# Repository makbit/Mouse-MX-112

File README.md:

# Mouse MX-112 - Free computer mouse with USB and PS/2 interfaces

This is a computer mouse with USB and PS/2 intefaces. There are 3 buttons and a wheel. The PCB is designed to be placed in a cheap plastic case manufactured in china. I have used the plastic case and lenses from the RX-112 mouse as a donor.

The mouse is compatible with Windows and Linux OS.

The device is based on a Silabs 8-bit MCU [EFM8UB20F32](https://www.silabs.com/mcu/8-bit/efm8-universal-bee/device.efm8ub20f32g-qfp32). This MCU has a Fullspeed USB controller and adjustable internal oscillator.

### Advantages of this mouse:
* Open hardware and software design;
* Compliant to hardware and software specification;
* Popular optical sensor ADNS-5050 with 1000+cpi and 8g;
* All electronic components are available in your local shop;
* I use it myself.

The [`Hardware`](Hardware) folder contains Eagle CAD 9 schematics files. The board schematics can be found in the[`Hardware/Mouse-112-sh.png`](Hardware/Mouse-112-sh.png) file.

The firmware is under development...

##### Some pictures of this Mouse MX-112:cool:

### Project Info

### TODO :pen:
 - [X] Solder;
 - [X] Test hardware;
 - [ ] Write firmware;
 - [ ] Test firmware;
 - [ ] Find a sponsor :smile:

[GitHub readme tips&tricks](https://help.github.com/articles/basic-writing-and-formatting-syntax/)

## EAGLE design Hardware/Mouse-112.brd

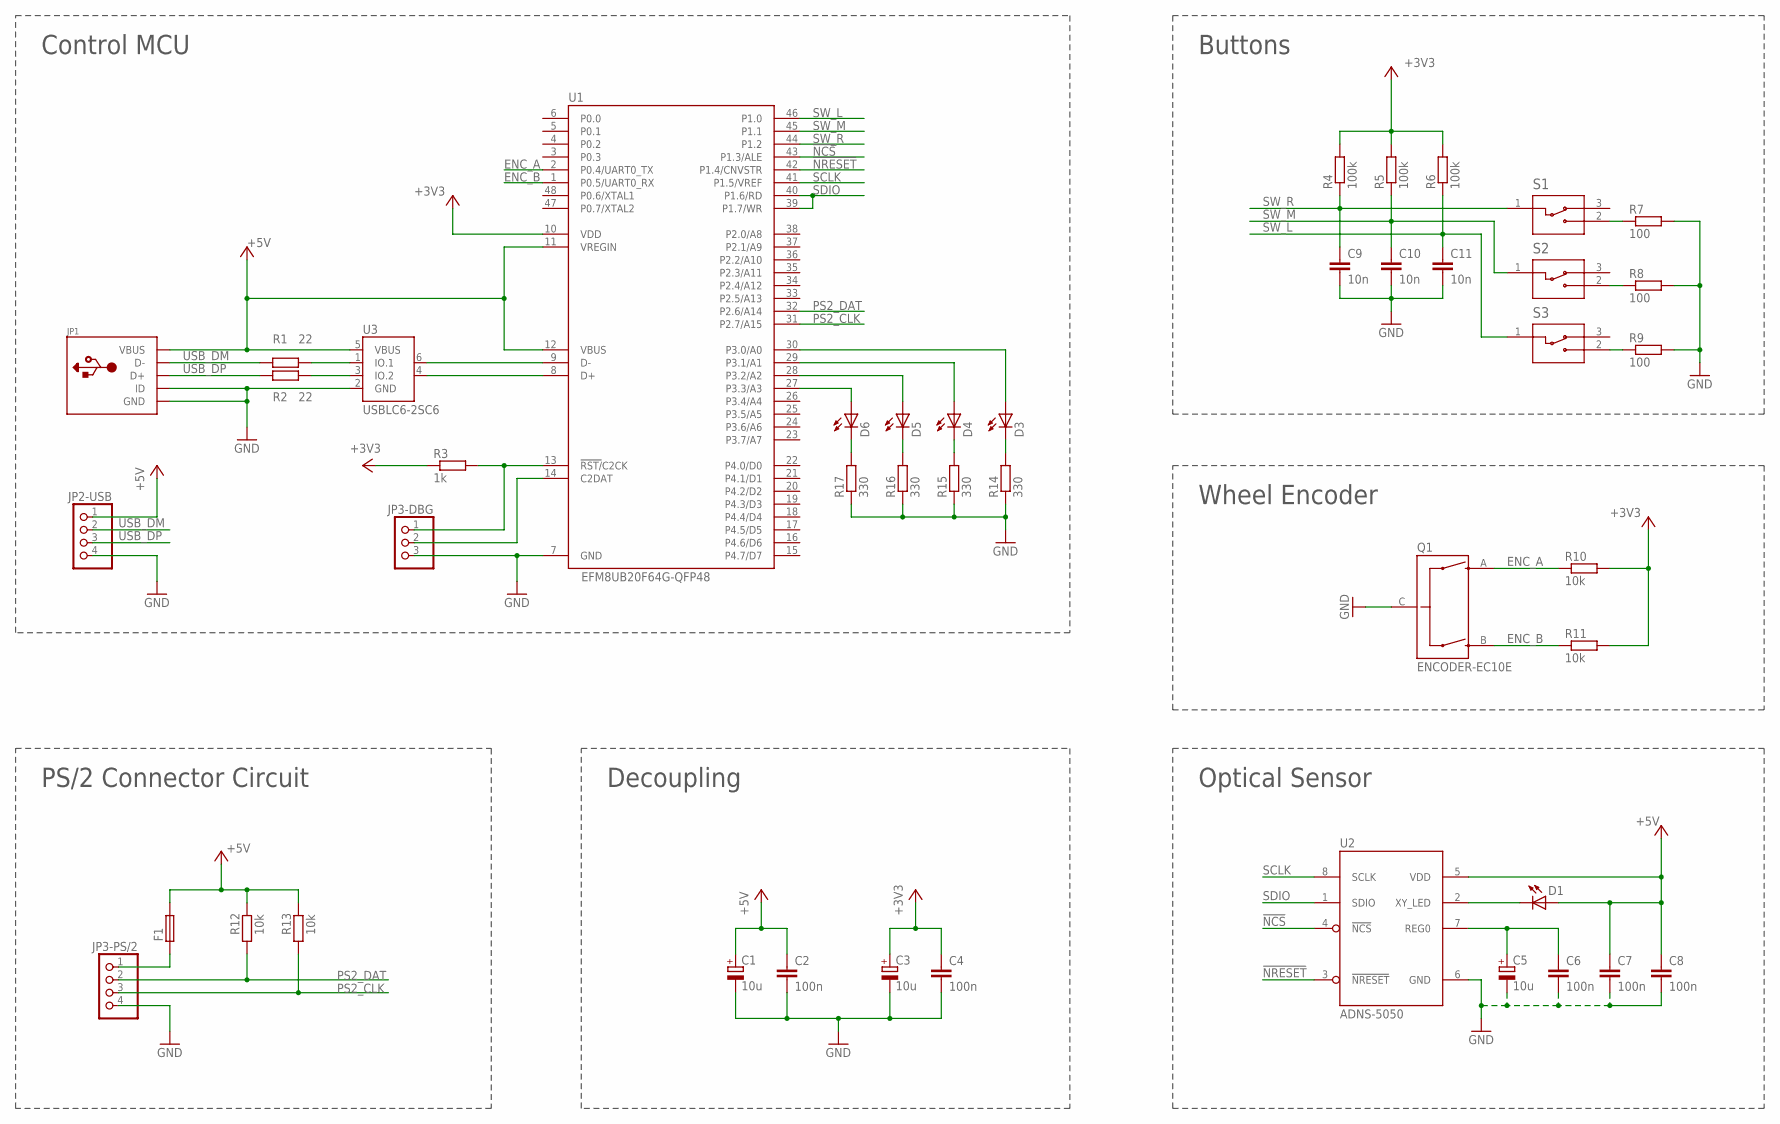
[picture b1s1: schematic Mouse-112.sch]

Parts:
C1, C3, C5: 10u; RCL-1206F-POL
C2, C4, C6, C7, C8: 100n; RCL-0805F
C9, C10, C11: 10n; RCL-0805F
D1: LED5MM
D3, D4, D5, D6: LEDLED-0805F; LED-0805F
F1: FUSE-NSMF; RCL-1206F
JP1: USB-MINI; USB-MINIB
JP2-USB, JP3-PS/2: PINHD-1X4; 1X04
JP3-DBG: PINHD-1X3; 1X03
Q1: ENCODER-EC10E; ENCODER-10MM
R1, R2: 22; RCL-0805F
R3: 1k; RCL-0805F
R4, R5, R6: 100k; RCL-0805F
R7, R8, R9: 100; RCL-0805F
R10, R11, R12, R13: 10k; RCL-0805F
R14, R15, R16, R17: 330; RCL-0805F
S1, S2, S3: SWITCH-D2F-01; SWITCH-D2F-01L-12.8X5.8MM
U1: EFM8UB20F64G-QFP48; QFP48-7X7-0P5MM
U2: ADNS-5050; ADNS-5050-DIP-8
U3: USBLC6-2SC6; SOT-23-6L

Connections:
!NCS: U1.43 (P1.3/ALE), U2.4 (!NCS)
!NRESET: U1.42 (P1.4/CNVSTR), U2.3 (!NRESET)
+3V3: C3.+, C4.1, R3.1, R4.2, R5.2, R6.2, R10.2, R11.2, U1.10 (VDD)
+5V: C1.+, C2.1, C7.1, C8.1, D1.A, F1.2, JP1.VBUS, JP2-USB.1, R12.2, R13.2, U1.11 (VREGIN), U1.12 (VBUS), U2.5 (VDD), U3.5 (VBUS)
C2CK: JP3-DBG.1, R3.2, U1.13 (!RST/!C2CK)
C2DAT: JP3-DBG.2, U1.14 (C2DAT)
ENC_A: Q1.A, R10.1, U1.2 (P0.4/UART0_TX)
ENC_B: Q1.B, R11.1, U1.1 (P0.5/UART0_RX)
GND: C1.-, C2.2, C3.-, C4.2, C5.-, C6.2, C7.2, C8.2, C9.2, C10.2, C11.2, JP1.GND, JP1.ID, JP2-USB.4, JP3-DBG.3, JP3-PS/2.4, Q1.C, R7.2, R8.2, R9.2, R14.1, R15.1, R16.1, R17.1, U1.7 (GND), U2.6 (GND), U3.2 (GND)
unnamed: D1.K (C), U2.2 (XY_LED)
unnamed: D4.A, U1.29 (P3.1/A1)
unnamed: R2.2, U3.3 (IO.2)
unnamed: R1.2, U3.1 (IO.1)
unnamed: D3.A, U1.30 (P3.0/A0)
unnamed: D4.C, R15.2
unnamed: U1.9 (D-), U3.6 (IO_1)
unnamed: U1.8 (D+), U3.4 (IO_2)
unnamed: D3.C, R14.2
unnamed: F1.1, JP3-PS/2.1
unnamed: D5.C, R16.2
unnamed: R7.1, S1.2
unnamed: R8.1, S2.2
unnamed: R9.1, S3.2
unnamed: D5.A, U1.28 (P3.2/A2)
unnamed: D6.A, U1.27 (P3.3/A3)
unnamed: D6.C, R17.2
PS2_CLK: JP3-PS/2.3, R13.1, U1.31 (P2.7/A15)
PS2_DAT: JP3-PS/2.2, R12.1, U1.32 (P2.6/A14)
REG0: C5.+, C6.1, U2.7 (REG0)
SCLK: U1.41 (P1.5/VREF), U2.8 (SCLK)
SDIO: U1.39 (P1.7/WR), U1.40 (P1.6/RD), U2.1 (SDIO)
SW_L: C11.1, R6.1, S3.1, U1.46 (P1.0)
SW_M: C10.1, R5.1, S2.1, U1.45 (P1.1)
SW_R: C9.1, R4.1, S1.1, U1.44 (P1.2)
USB_DM: JP1.D-, JP2-USB.2, R1.1
USB_DP: JP1.D+, JP2-USB.3, R2.1

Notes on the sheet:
Wheel Encoder
Buttons
Optical Sensor
Control MCU
Decoupling
PS/2 Connector Circuit

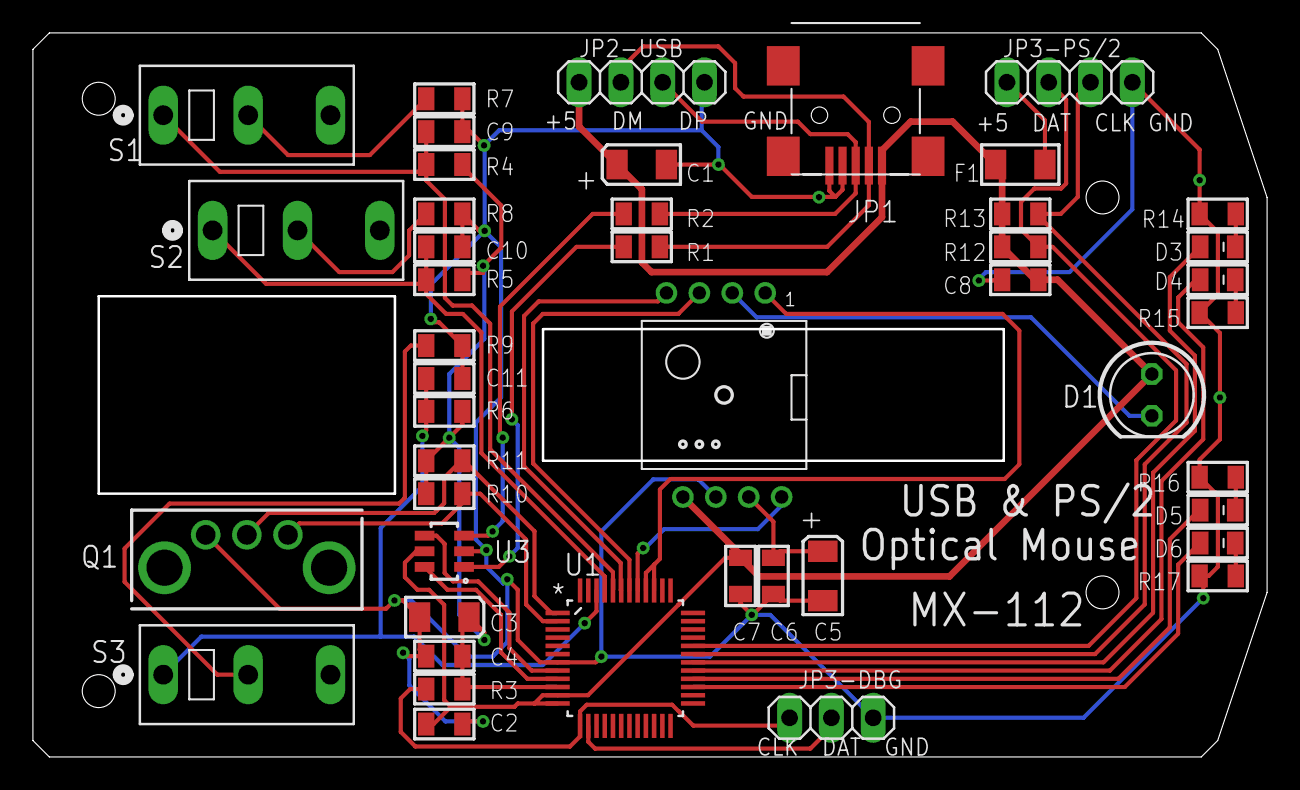
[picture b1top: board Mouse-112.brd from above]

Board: 2 copper layers, 75.0 x 44.0 mm, 45 parts (0 on the bottom side), 36 nets.

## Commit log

2023-06-30 Update README.md
    URL error fixed
